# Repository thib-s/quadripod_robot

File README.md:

Quadripod robot
===================

All the files to build a quadripod, including 3d model, eagle files and ROS code.

Disclaimer
==========

This is a personal project, this means that this quadripod was build in a single exemplary. It worked fine for me, but i cannot be held responsible if you fry somehing using my plans.

Repository organization
=======================

3D
--

Contains stl for 3d print the robot, there are the original files from hackaday: [https://hackaday.io/project/9334-kame-esp8266-based-quadruped]. It contains also the modified STL to build the same base with mg996 servos.

Quadripod\_board
-------------

Contains the eagle files for the pcb manufacturing.

Code
----

Contains the code that runs on the raspberry pi zero:
 - The folder `catkin\_ws` contains the node to run locally on the robot. 
 - The folder `camera\_calibration` contains the files to calibrate the camera. 
 - The folder `teleop\_ws contains` the nodes to control the robot remotely using a joystick.
 
ROSpbianZero
------------

Contains the tutorial to setup the raspberry pi zero:
 1. install raspbian lite
 2. compile and install ros kinetic (perception)
 3. setup the service to start a launchfile at boot
 4. setup the wifi AP

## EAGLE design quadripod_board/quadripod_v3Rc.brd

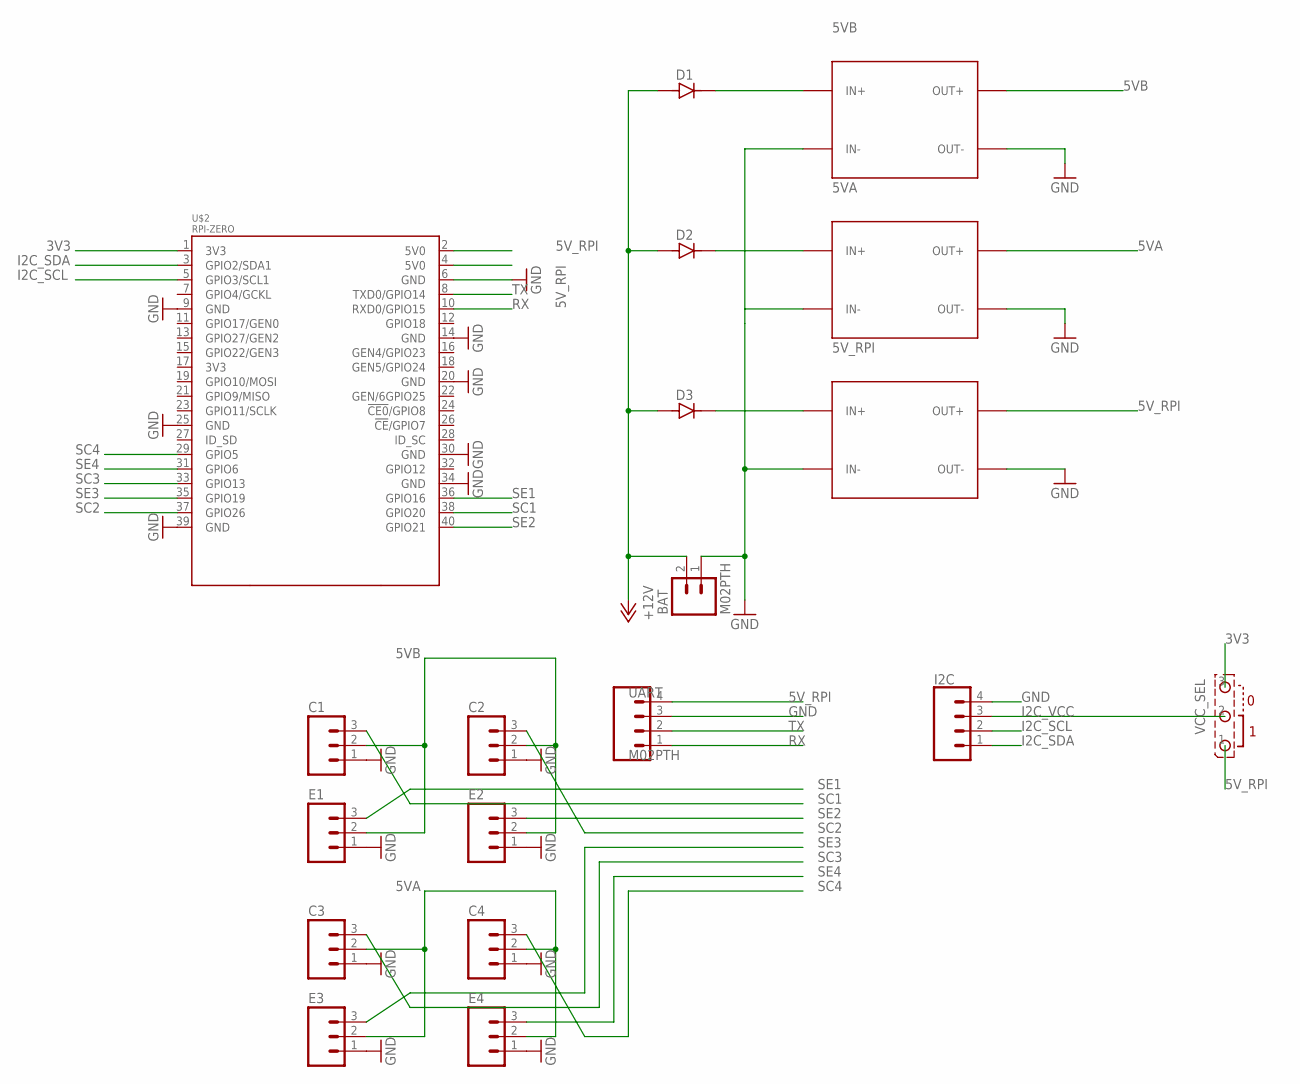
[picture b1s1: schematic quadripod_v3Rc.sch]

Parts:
5VA, 5VB, 5V_RPI: DC-DC-STEP-DOWN-LM2596
BAT: M02PTH; 1X02_LONGPADS
C1, C2, C3, C4: M03LONGPADS; 1X03_LONGPADS
D1, D2, D3: DIODES_DIODE/DO41; DIODES_DO41
E1, E2, E3, E4: M03LONGPADS; 1X03_LONGPADS
I2C: CONN_04LONGPADS; 1X04_LONGPADS
U$2: RPI-ZERO; RASPBERRYPI_BASTELSTUBE_V13_RASPI_BOARD_B+_FULL
UART: M02PTH; 1X04_LONGPADS
VCC_SEL: STCMS_3/CMS; STCMS_3

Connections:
3V3: U$2.1 (3V3), VCC_SEL.3
5VA: 5VA.OUT+, C3.2, C4.2, E3.2, E4.2
5VB: 5VB.OUT+, C1.2, C2.2, E1.2, E2.2
5V_RPI: 5V_RPI.OUT+, U$2.2 (5V0), U$2.4 (5V0), UART.4, VCC_SEL.1
+12V: BAT.2, D1.A, D2.A, D3.A
GND: 5VA.IN-, 5VA.OUT-, 5VB.IN-, 5VB.OUT-, 5V_RPI.IN-, 5V_RPI.OUT-, BAT.1, C1.1, C2.1, C3.1, C4.1, E1.1, E2.1, E3.1, E4.1, I2C.4, U$2.6 (GND), U$2.9 (GND), U$2.14 (GND), U$2.20 (GND), U$2.25 (GND), U$2.30 (GND), U$2.34 (GND), U$2.39 (GND), UART.3
I2C_SCL: I2C.2, U$2.5 (GPIO3/SCL1)
I2C_SDA: I2C.1, U$2.3 (GPIO2/SDA1)
I2C_VCC: I2C.3, VCC_SEL.2
unnamed: 5VB.IN+, D1.K
unnamed: 5V_RPI.IN+, D3.K
unnamed: 5VA.IN+, D2.K
RX: U$2.10 (RXD0/GPIO15), UART.1
SC1: C1.3, U$2.38 (GPIO20)
SC2: C2.3, U$2.37 (GPIO26)
SC3: C3.3, U$2.33 (GPIO13)
SC4: C4.3, U$2.29 (GPIO5)
SE1: E1.3, U$2.36 (GPIO16)
SE2: E2.3, U$2.40 (GPIO21)
SE3: E3.3, U$2.35 (GPIO19)
SE4: E4.3, U$2.31 (GPIO6)
TX: U$2.8 (TXD0/GPIO14), UART.2

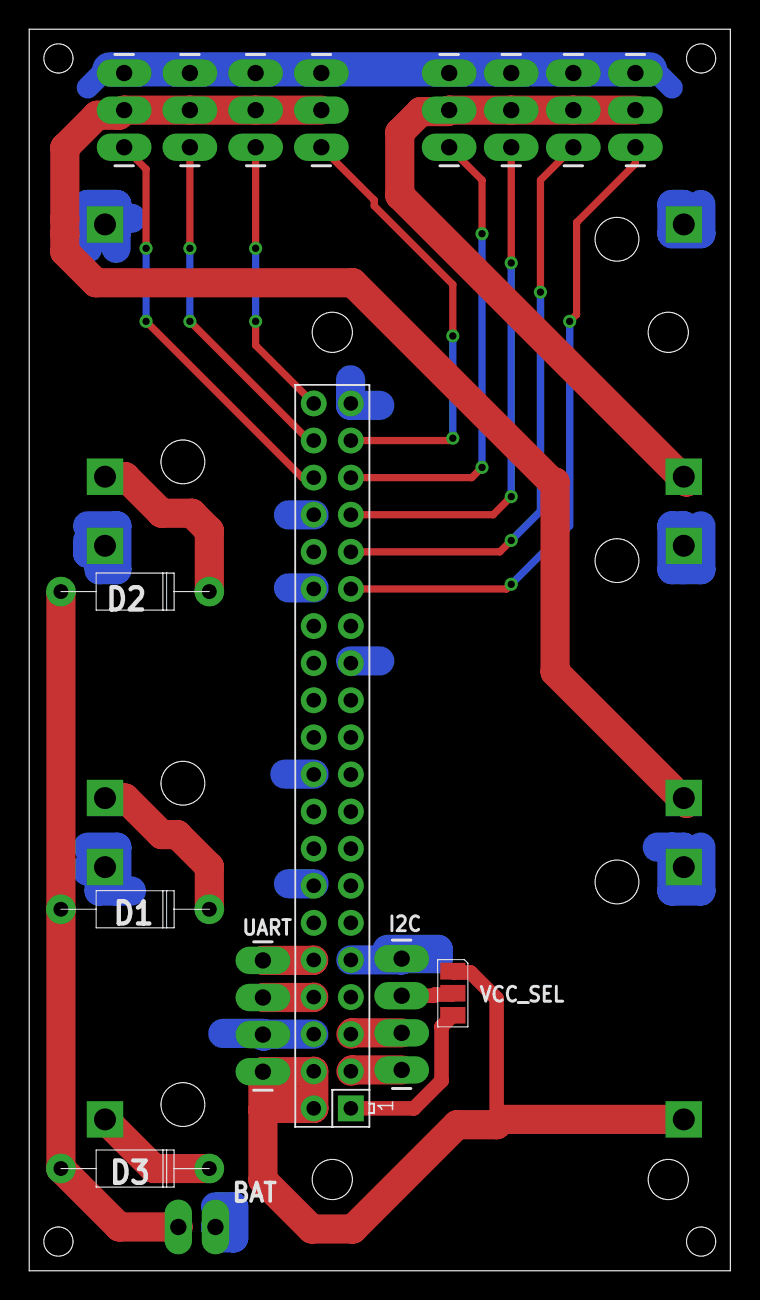
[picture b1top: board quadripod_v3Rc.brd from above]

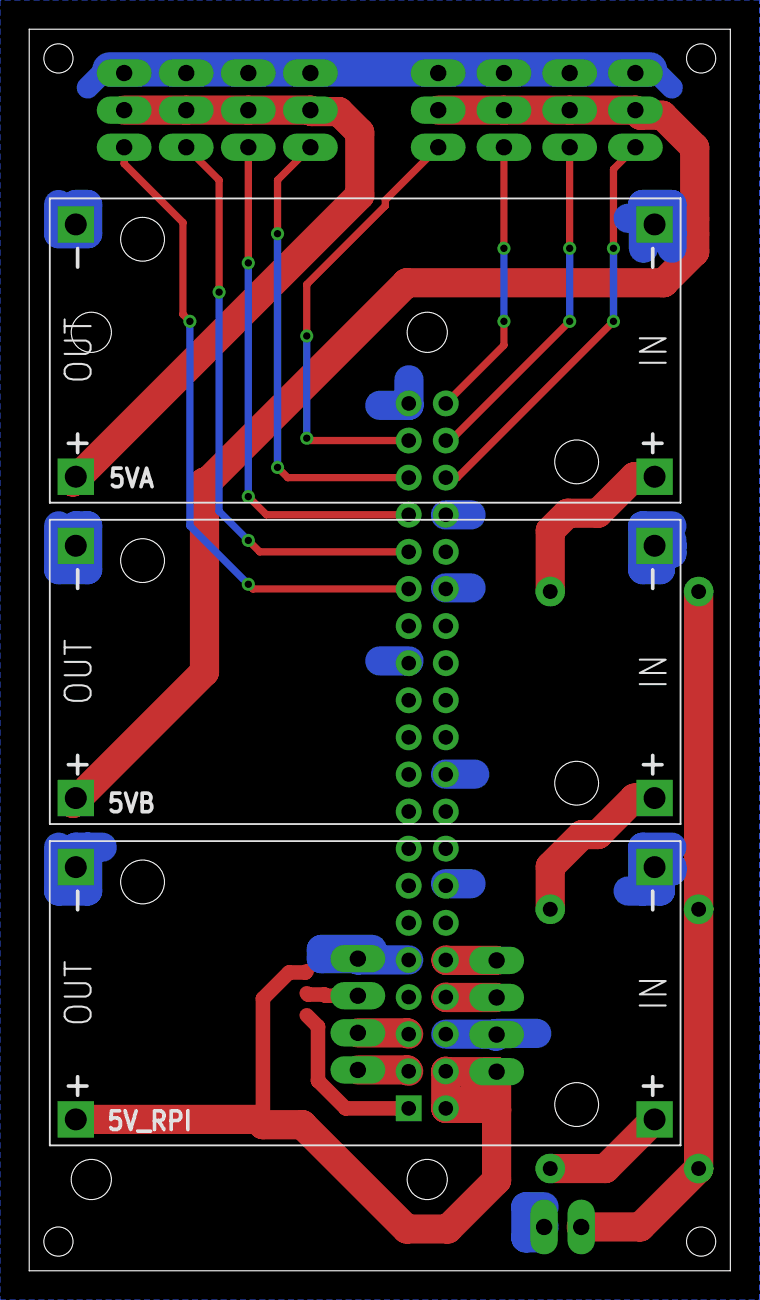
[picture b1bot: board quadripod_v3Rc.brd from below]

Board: 2 copper layers, 48.0 x 85.0 mm, 19 parts (4 on the bottom side), 22 nets.

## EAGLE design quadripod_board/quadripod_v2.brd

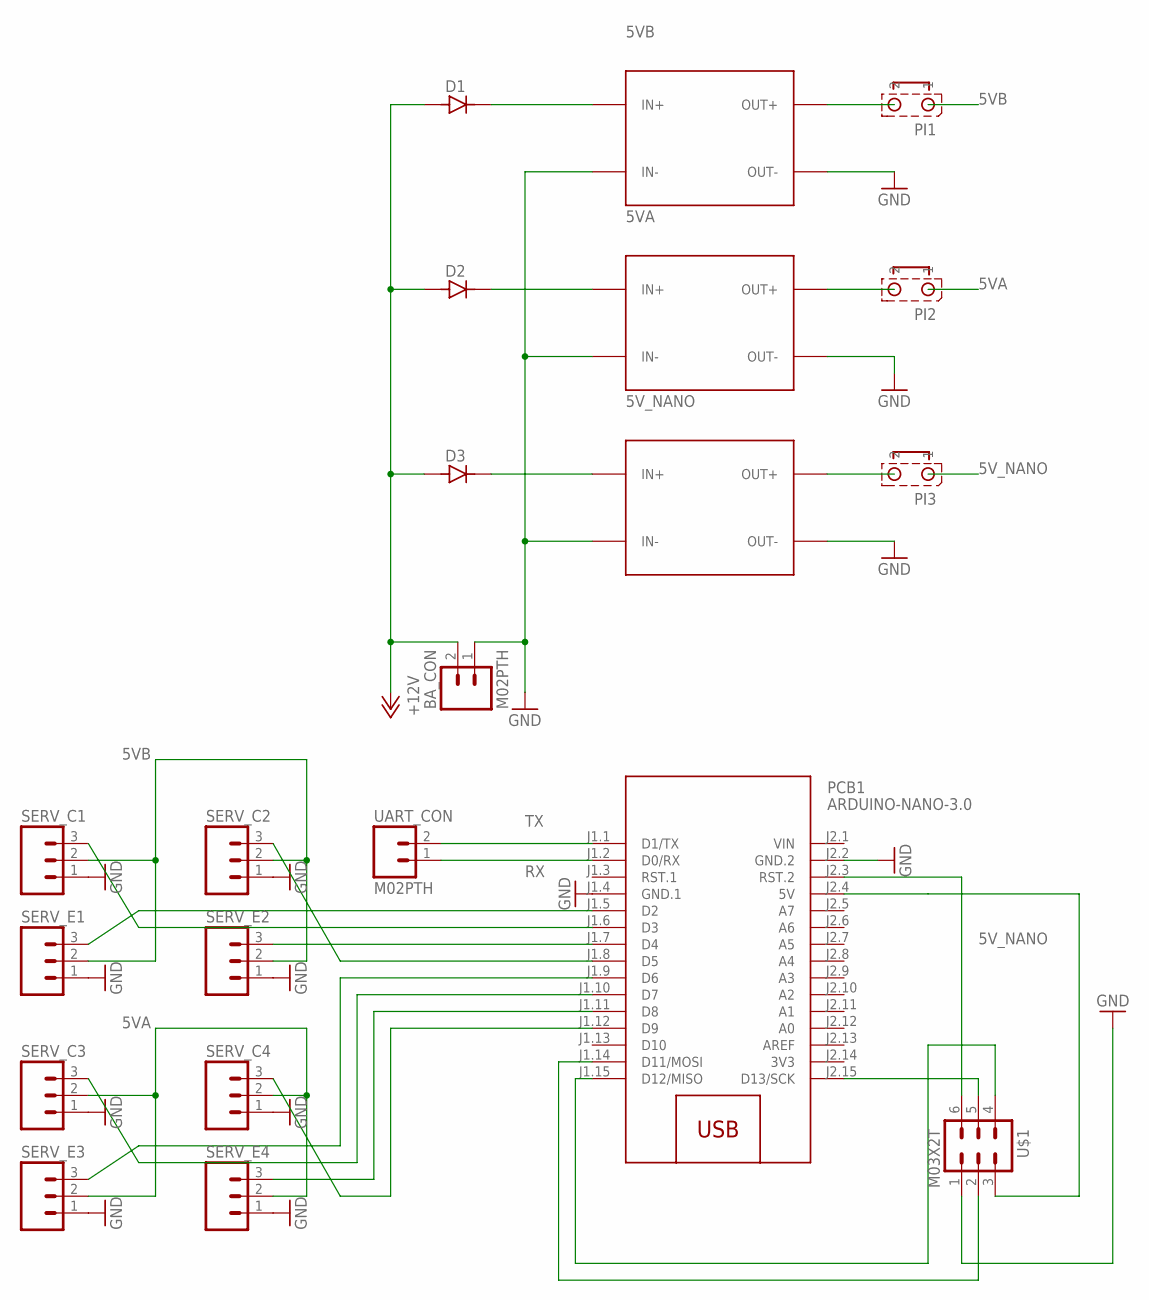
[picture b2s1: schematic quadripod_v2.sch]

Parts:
5VA, 5VB, 5V_NANO: DC-DC-STEP-DOWN-LM2596
BA_CON: M02PTH; 1X02
D1, D2, D3: DIODES_DIODE/DO41; DIODES_DO41
PCB1: ARDUINO-NANO-3.0
PI1, PI2, PI3: STCMS_2
SERV_C1, SERV_C2, SERV_C3, SERV_C4: M03LONGPADS; 1X03_LONGPADS
SERV_E1, SERV_E2, SERV_E3, SERV_E4: M03LONGPADS; 1X03_LONGPADS
U$1: M03X2T; 2X03
UART_CON: M02PTH; 1X02

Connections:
3V3: PCB1.J2.14 (3V3)
5VA: PI2.1, SERV_C3.2, SERV_C4.2, SERV_E3.2, SERV_E4.2
5VB: PI1.1, SERV_C1.2, SERV_C2.2, SERV_E1.2, SERV_E2.2
5V_NANO: PCB1.J2.4 (5V), PI3.1, U$1.3
+12V: BA_CON.2, D1.A, D2.A, D3.A
GND: 5VA.IN-, 5VA.OUT-, 5VB.IN-, 5VB.OUT-, 5V_NANO.IN-, 5V_NANO.OUT-, BA_CON.1, PCB1.J1.4 (GND.1), PCB1.J2.2 (GND.2), SERV_C1.1, SERV_C2.1, SERV_C3.1, SERV_C4.1, SERV_E1.1, SERV_E2.1, SERV_E3.1, SERV_E4.1, U$1.1
unnamed: 5VB.IN+, D1.K
unnamed: PCB1.J1.5 (D2), SERV_E1.3
unnamed: 5VA.IN+, D2.K
unnamed: 5V_NANO.IN+, D3.K
unnamed: PCB1.J1.6 (D3), SERV_C1.3
unnamed: PCB1.J1.7 (D4), SERV_E2.3
unnamed: PCB1.J1.8 (D5), SERV_C2.3
unnamed: PCB1.J1.9 (D6), SERV_E3.3
unnamed: PCB1.J1.10 (D7), SERV_C3.3
unnamed: PCB1.J1.11 (D8), SERV_E4.3
unnamed: PCB1.J1.12 (D9), SERV_C4.3
unnamed: 5VB.OUT+, PI1.2
unnamed: 5VA.OUT+, PI2.2
unnamed: 5V_NANO.OUT+, PI3.2
unnamed: PCB1.J1.14 (D11/MOSI), U$1.2
unnamed: PCB1.J2.3 (RST.2), U$1.6
unnamed: PCB1.J2.15 (D13/SCK), U$1.5
unnamed: PCB1.J1.15 (D12/MISO), U$1.4
RX: PCB1.J1.2 (D0/RX), UART_CON.1
TX: PCB1.J1.1 (D1/TX), UART_CON.2
VIN: PCB1.J2.1 (VIN)

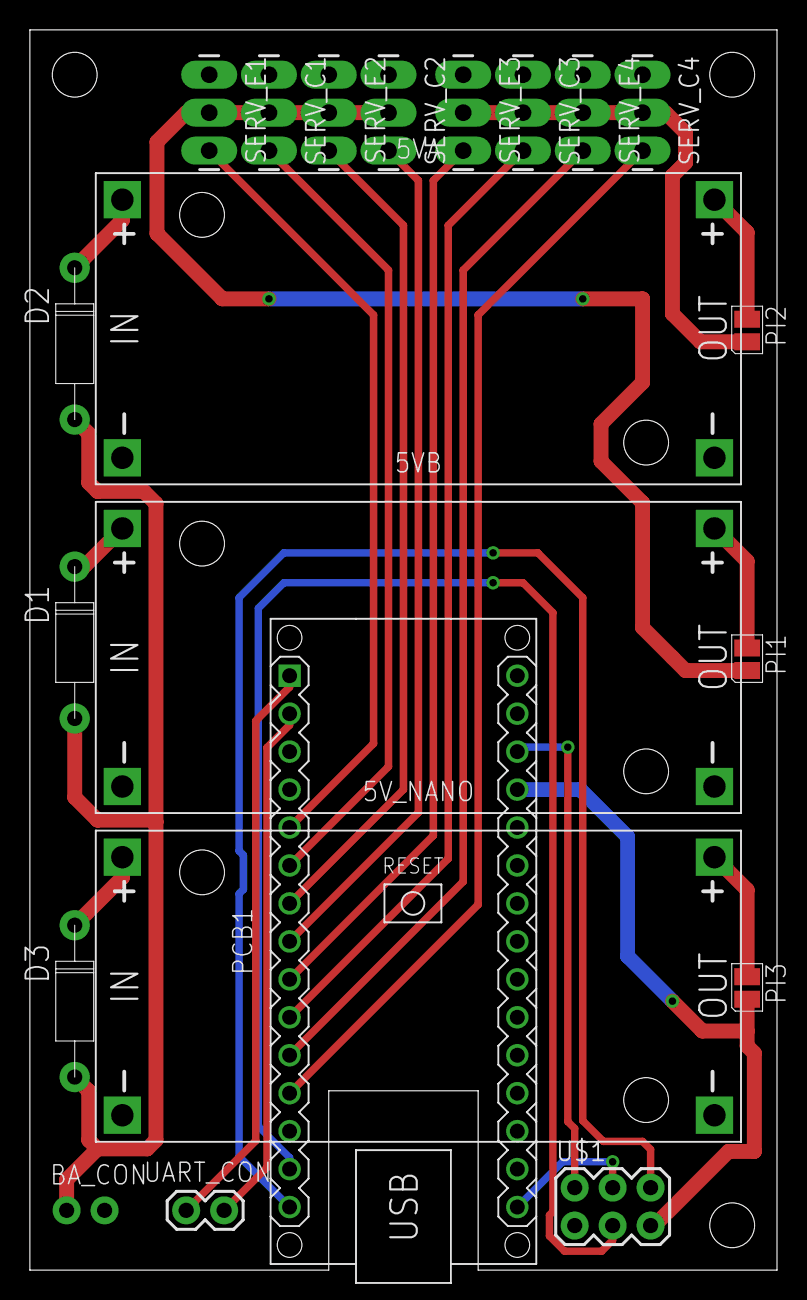
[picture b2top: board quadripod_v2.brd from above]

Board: 2 copper layers, 50.0 x 83.0 mm, 21 parts (1 on the bottom side), 25 nets.

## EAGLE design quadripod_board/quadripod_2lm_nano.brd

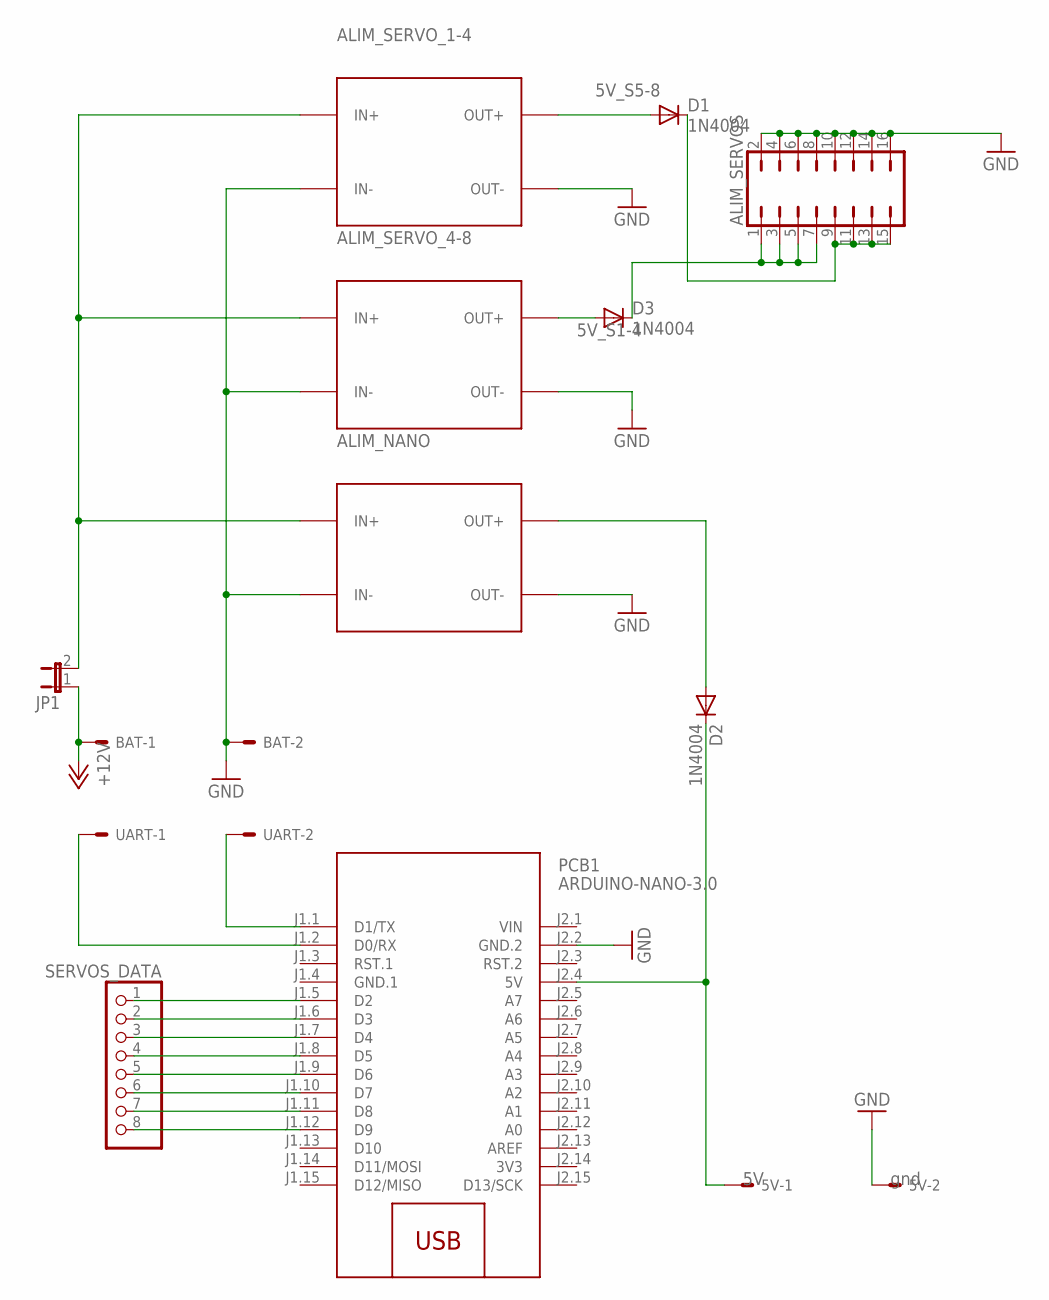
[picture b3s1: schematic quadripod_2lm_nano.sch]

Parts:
5V: 332-02
ALIM_NANO: DC-DC-STEP-DOWN-LM2596
ALIM_SERVOS: JP8Q
ALIM_SERVO_1-4, ALIM_SERVO_4-8: DC-DC-STEP-DOWN-LM2596
BAT: 332-02; VOLTAGE 12V
D1, D2, D3: 1N4004; DO41-10
JP1: JP1E; JP1
PCB1: ARDUINO-NANO-3.0
SERVOS_DATA: PINHD-1X8; 1X08
UART: 332-02

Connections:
3V3: PCB1.J2.14 (3V3)
5V_NANO: ALIM_NANO.OUT+, D2.A
5V_S1-4: ALIM_SERVOS.1, ALIM_SERVOS.3, ALIM_SERVOS.5, ALIM_SERVOS.7, D3.C
5V_S5-8: ALIM_SERVOS.9, ALIM_SERVOS.11, ALIM_SERVOS.13, ALIM_SERVOS.15, D1.C
+12V: BAT.1, JP1.1
GND: 5V.2, ALIM_NANO.IN-, ALIM_NANO.OUT-, ALIM_SERVOS.2, ALIM_SERVOS.4, ALIM_SERVOS.6, ALIM_SERVOS.8, ALIM_SERVOS.10, ALIM_SERVOS.12, ALIM_SERVOS.14, ALIM_SERVOS.16, ALIM_SERVO_1-4.IN-, ALIM_SERVO_1-4.OUT-, ALIM_SERVO_4-8.IN-, ALIM_SERVO_4-8.OUT-, BAT.2, PCB1.J2.2 (GND.2)
GND.1: PCB1.J1.4 (GND.1)
unnamed: ALIM_SERVO_4-8.OUT+, D3.A
unnamed: PCB1.J1.5 (D2), SERVOS_DATA.1
unnamed: 5V.1, D2.C, PCB1.J2.4 (5V)
unnamed: ALIM_SERVO_1-4.OUT+, D1.A
unnamed: PCB1.J1.6 (D3), SERVOS_DATA.2
unnamed: PCB1.J1.7 (D4), SERVOS_DATA.3
unnamed: PCB1.J1.8 (D5), SERVOS_DATA.4
unnamed: PCB1.J1.9 (D6), SERVOS_DATA.5
unnamed: PCB1.J1.10 (D7), SERVOS_DATA.6
unnamed: PCB1.J1.11 (D8), SERVOS_DATA.7
unnamed: PCB1.J1.12 (D9), SERVOS_DATA.8
unnamed: PCB1.J1.2 (D0/RX), UART.1
unnamed: PCB1.J1.1 (D1/TX), UART.2
unnamed: ALIM_NANO.IN+, ALIM_SERVO_1-4.IN+, ALIM_SERVO_4-8.IN+, JP1.2
VIN: PCB1.J2.1 (VIN)

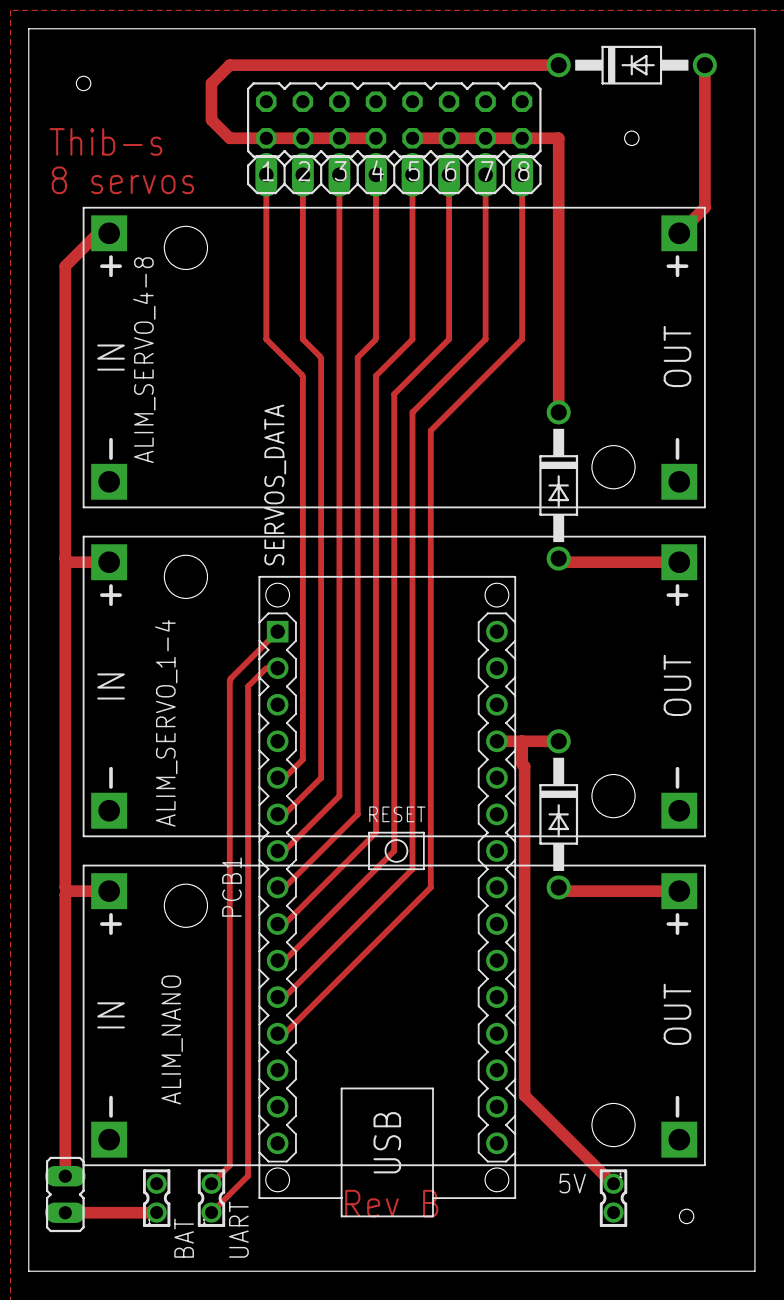
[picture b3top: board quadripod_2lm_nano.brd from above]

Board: 2 copper layers, 50.5 x 86.4 mm, 13 parts (0 on the bottom side), 19 nets.

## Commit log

2018-07-05 first commit, bien dodu on dirait
2018-07-12 board revision, added diodes to avoid powering the servos while programming the arduino
2018-07-12 add correction system and values on servos test
2018-07-12 fix des index, ajout des offset sur les servos, et de la doc!
2018-07-15 ajout de reglage d'amplitude pour la demarche + plein de fonctions pour regler les params dynamiquement
2018-07-23 3d model of camera + rpi holder
2018-07-23 added uart interpreter
2018-10-27 slowed down the uart as pi zero use it for bt
2018-10-27 added disclamer, just in case
2018-10-27 added ros nodes
2018-10-27 just 4 fun
2018-10-27 added pic in README
2019-03-17 added functions tilt_body and raise_body
2019-03-17 command parsing with function pointer
2019-07-19 update board, some checks to come
2019-09-18 upate of the board
2019-09-18 update base controller to use new archi with standalone rpi
2019-09-26 stable architecture & code refacto
2019-09-26 added visuals
2019-09-26 tutorial to install ROS on raspberry pi zero
2019-09-26 added teleop workspace
2019-10-01 clean walk_controller
2019-10-01 added line following and image calibration nodes
2019-10-01 fixed bug in line follower
2019-10-01 quick fix compile error on robot
2019-10-01 update bringup launchfile
2019-10-01 these params works a 2.0 speed
2019-10-03 first attempt to make all this code run on rpi zero
2019-10-03 c++ reprojection node start to be promising
2019-10-03 reprojection node c++ ok
2019-10-03 added node to mux autopilot and manual pilot
2019-10-03 use start button to disable manual control
2019-10-05 commit before revert
2019-10-06 commit post toulouse robot race
2019-10-06 camera reprojection script
2019-10-06 no image analysis => back to 30fps
2019-10-06 large renaming campain
2019-10-06 quick fix of environment var on the rasberry
2019-10-06 some settings to make if work properly with teleop
2019-11-03 added bound to twist and pose commands
2019-11-03 fix bug in joystick button mapping

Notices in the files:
parts and their libraries:
diy-modules: Released under the Creative Commons Attribution 4.0 International License: http://creativecommons.org/licenses/by/4.0
SparkFun-Connectors: Licensing: Creative Commons ShareAlike 4.0 International - https://creativecommons.org/licenses/by-sa/4.0
